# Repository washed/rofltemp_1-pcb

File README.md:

# rofltemp_1-pcb

This is the circuit schematic and board layout project for the ROFLtemp-1 multi-purpose
RTD thermometer.
# WARNING! DO NOT BUILD WITH THESE DESIGN FILES! Several stupid errors are in this layout that will be corrected in the final version!

# Features:
 - High accuracy RTD (PT1000) 4-wire measurement
 - Filtering for measurement inputs for high immunity in noisy enviroments (I'm looking at you, induction stoves!)
 - USB connectivity for LiPo battery charging, firmware update and data-logging
 - High brightness 7-segment LED display for good readability even in daylight
 - 0.1° resolution on 3-digit display -> above 99.9 displayed resolution will drop to 1°
 - Integrated fast charging, power path management and buck/boost regulator for efficient battery use and continous operation if plugged in

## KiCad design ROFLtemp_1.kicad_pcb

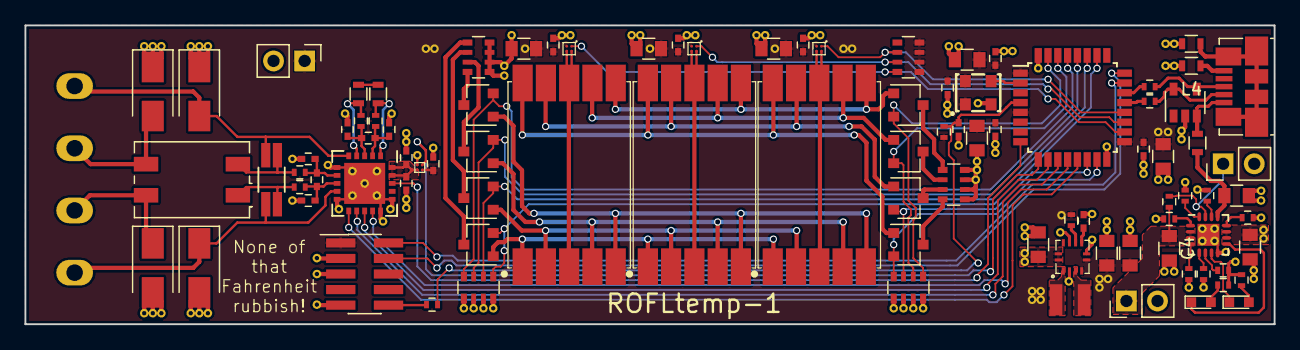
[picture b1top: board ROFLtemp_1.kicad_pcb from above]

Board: 2 copper layers, 102.0 x 24.4 mm, 96 parts (0 on the bottom side), 81 nets.

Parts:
C1: 1u 25V; C_0805
C2, C3, C5, C17, C19, C21, C22, C24, C25, C27, C29: 100n 16V; C_0402
C4, C6: 4u7 25V; C_0805
C7: 10u 25V; C_0805
C8, C11, C12, C13: 1n; C_0402
C9, C10: 10n; C_0402
C14: 1n3 16V; C_0402
C15, C16: 10u 6V3; C_0805
C18, C20, C23, C26, C28, C30: 1u 16V; C_0805
D1, D2: LED_ALT; LED_0603
D3, D4, D5, D6: D_TVS; D_SMA_Standard
D7: SP0504BAHT; SOT-23-5
J1: USB_OTG; USB_Micro-B_Molex_47346-0001
J2: CONN_02X05; Pin_Header_Straight_2x05_Pitch1.27mm_SMD
L1: LQM2HPN1R5MG0L; Neosid_Inductor_SM-NE29_SMD1008
L2: WE-SL2; L_CommonMode_Wuerth_WE-SL2
L3, L4, L5: WE-CBF 742792651; L_0603
P1, P2: CONN_01X02; PM_5.08_2
P3, P4: CONN_01X02; Pin_Header_Straight_1x02_Pitch2.54mm
Q1: ASEM1
Q2, Q3, Q5, Q6, Q8, Q9, Q10, Q12: DMN1019USN; SC-59
Q4, Q7, Q11: DMP1100UCB4; X2-WLB0808-4
R1, R2, R6, R9, R21: 10k; R_0402
R3: DNI; R_0402
R4, R5, R10, R18: 100k; R_0402
R7, R8: 1k5; R_0402
R11, R12, R13, R14: TBD R; R_0402
R15: RTD PT1000 DNI; R_1206_RTD_SPLITPADS
R16: 2k 0.01%; R_0603
R17: 2K 0.01%; R_0603
R19, R20: 15R; R_0402
R22: 0R; R_0402
RN1, RN3, RN5: 10k; R_Array_Convex_4x0603
RN2, RN4: 68R; R_Array_Convex_4x0603
SW1: SW_SPST; Pin_Header_Straight_1x02_Pitch2.54mm
U1: TPS2290x; TPS229x
U2: BQ24079; QFN-16-1EP_3x3mm_Pitch0.5mm
U3: MAX31865; QFN-20-1EP_5x5mm_Pitch0.65mm
U4: STM32F042K6Tx; LQFP-32_7x7mm_Pitch0.8mm
U5: TPS63051; RWM0012A
U6, U7, U8: 7SEGMENT_CA; VDMx10.0

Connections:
+3V3: C2.1, C15.1, C16.1, C17.1, C18.1, C19.1, C20.1, C21.1, C23.1, C24.1, C25.1, C26.1, C27.1, C28.1, C29.1, C30.1, J2.1, P4.1, Q1.1, Q1.4, Q4.2, Q7.2, Q11.2, R18.2, R21.2, RN5.1, RN5.2, RN5.3, RN5.4, U1.A1, U4.1, U4.5, U4.17, U5.4, U5.5
+5V: C1.1, L5.1, U2.13
+BATT: C4.1, P3.1, R1.2, U2.2, U2.3
/7SEG_0: Q11.1, RN5.8, U4.18
/7SEG_1: Q4.1, RN5.7, U4.19
/7SEG_2: Q7.1, RN5.6, U4.20
/7SEG_A: Q2.2, RN3.6, U4.30
/7SEG_B: Q3.2, RN3.5, U4.31
/7SEG_C: Q5.2, RN1.7, U4.28
/7SEG_D: Q6.2, RN1.6, U4.27
/7SEG_DP: Q12.2, RN1.8, U4.29
/7SEG_E: Q8.2, RN1.5, U4.26
/7SEG_F: Q9.2, RN3.7, U4.14
/7SEG_G: Q10.2, RN3.8, U4.15
/OSC_IN: Q1.3, U4.2
/SPI1_CS: U3.13, U4.10
/SPI1_DR: U3.18, U4.8
/SPI1_MISO: U3.14, U4.12
/SPI1_MOSI: U3.11, U4.13
/SPI1_PWR: U1.B1, U4.9
/SPI1_SCK: U3.12, U4.11
/SYS_NRST: C22.1, R21.1, R22.2, U4.4
/SYS_SWCLK: J2.4, U4.24
/SYS_SWDIO: J2.2, U4.23
/USB_DM: D7.5, J1.2, R19.2
/USB_DP: D7.4, J1.3, R20.2
GND: C1.2, C2.2, C3.2, C4.2, C5.2, C6.2, C7.2, C8.1, C11.2, C12.1, C13.2, C14.2, C15.2, C16.2, C17.2, C18.2, C19.2, C20.2, C21.2, C22.2, C23.2, C24.2, C25.2, C26.2, C27.2, C28.2, C29.2, C30.2, D3.1, D4.2, D5.1, D6.2, D7.2, J2.3, J2.5, J2.9, L3.2, L4.2, P3.2, P4.2, Q1.2, R2.1, R3.1, R4.1, R5.1, R6.1, R9.1, RN1.1, RN1.2, RN1.3, RN1.4, RN2.1, RN2.2, RN2.3, RN2.4, RN3.1, RN3.2, RN3.3, RN3.4, RN4.1, RN4.2, RN4.3, RN4.4, SW1.2, U1.B2, U2.8, U2.17, U3.6, U3.10, U3.15, U3.16, U3.21, U4.16, U4.32, U5.2, U5.6, U5.9
unnamed: C3.1, C5.1, U1.A2, U3.19, U3.20
unnamed: C6.1, C7.1, R7.2, R8.2, R10.2, U2.10, U2.11, U5.11, U5.12
unnamed: C8.2, C9.1, R11.1, U3.2
unnamed: C10.1, C13.1, R13.1, U3.7
unnamed: C10.2, C11.1, R14.1, U3.8
unnamed: C9.2, C12.2, R12.1, U3.3
unnamed: C14.1, U5.7
unnamed: D1.1, U2.7
unnamed: D1.2, R7.1
unnamed: D2.1, U2.9
unnamed: D2.2, R8.1
unnamed: D3.2, L2.2, P1.1, R13.2, R15.1, U3.5
unnamed: D4.1, L2.1, P2.2, R14.2, R15.2, U3.9
unnamed: D5.2, L2.3, P1.2
unnamed: D6.1, L2.4, P2.1
unnamed: D7.3, J1.1, L5.2
unnamed: J1.5, L4.1
unnamed: J1.6, L3.1
unnamed: J2.10, R22.1
unnamed: L1.1, U5.1
unnamed: L1.2, U5.3
unnamed: Q2.1, U6.7, U7.7, U8.7
unnamed: Q2.3, RN2.6
unnamed: Q3.1, U6.6, U7.6, U8.6
unnamed: Q3.3, RN2.5
unnamed: Q4.3, Q4.4, U6.3, U6.8
unnamed: Q5.1, U6.4, U7.4, U8.4
unnamed: Q5.3, RN4.7
unnamed: Q6.1, U6.2, U7.2, U8.2
unnamed: Q6.3, RN4.6
unnamed: Q7.3, Q7.4, U7.3, U7.8
unnamed: Q8.1, U6.1, U7.1, U8.1
unnamed: Q8.3, RN4.5
unnamed: Q9.1, U6.9, U7.9, U8.9
unnamed: Q9.3, RN2.7
unnamed: Q10.1, U6.10, U7.10, U8.10
unnamed: Q10.3, RN2.8
unnamed: Q11.3, Q11.4, U8.3, U8.8
unnamed: Q12.1, U6.5, U7.5, U8.5
unnamed: Q12.3, RN4.8
unnamed: R1.1, SW1.1, U2.15
unnamed: R2.2, U2.4
unnamed: R3.2, U2.14
unnamed: R4.2, U2.12
unnamed: R5.2, U2.16
unnamed: R6.2, U2.1
unnamed: R9.2, U2.5
unnamed: R10.1, U2.6
unnamed: R11.2, R16.1, U3.1
unnamed: R12.2, R17.1, U3.4
unnamed: R16.2, R17.2
unnamed: R18.1, U5.8
unnamed: R19.1, U4.21
unnamed: R20.1, U4.22

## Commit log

2017-04-19 Begin power management circuitry
2017-04-27 Started adding battery and 7Seg circuit
2017-04-29 Add some more circuitry
2017-04-30 Finish schematic, start layout
2017-05-02 Finish first prototype version
2017-05-18 Improve readability for PCB population
2017-05-19 Add some production docs
2017-05-21 Change charger set resistor values
2017-05-25 Add README
